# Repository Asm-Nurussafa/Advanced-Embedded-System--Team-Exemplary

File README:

To see the results of the final simulation ,simulate the fin_decode_TB in modelsim,found in the project folder.

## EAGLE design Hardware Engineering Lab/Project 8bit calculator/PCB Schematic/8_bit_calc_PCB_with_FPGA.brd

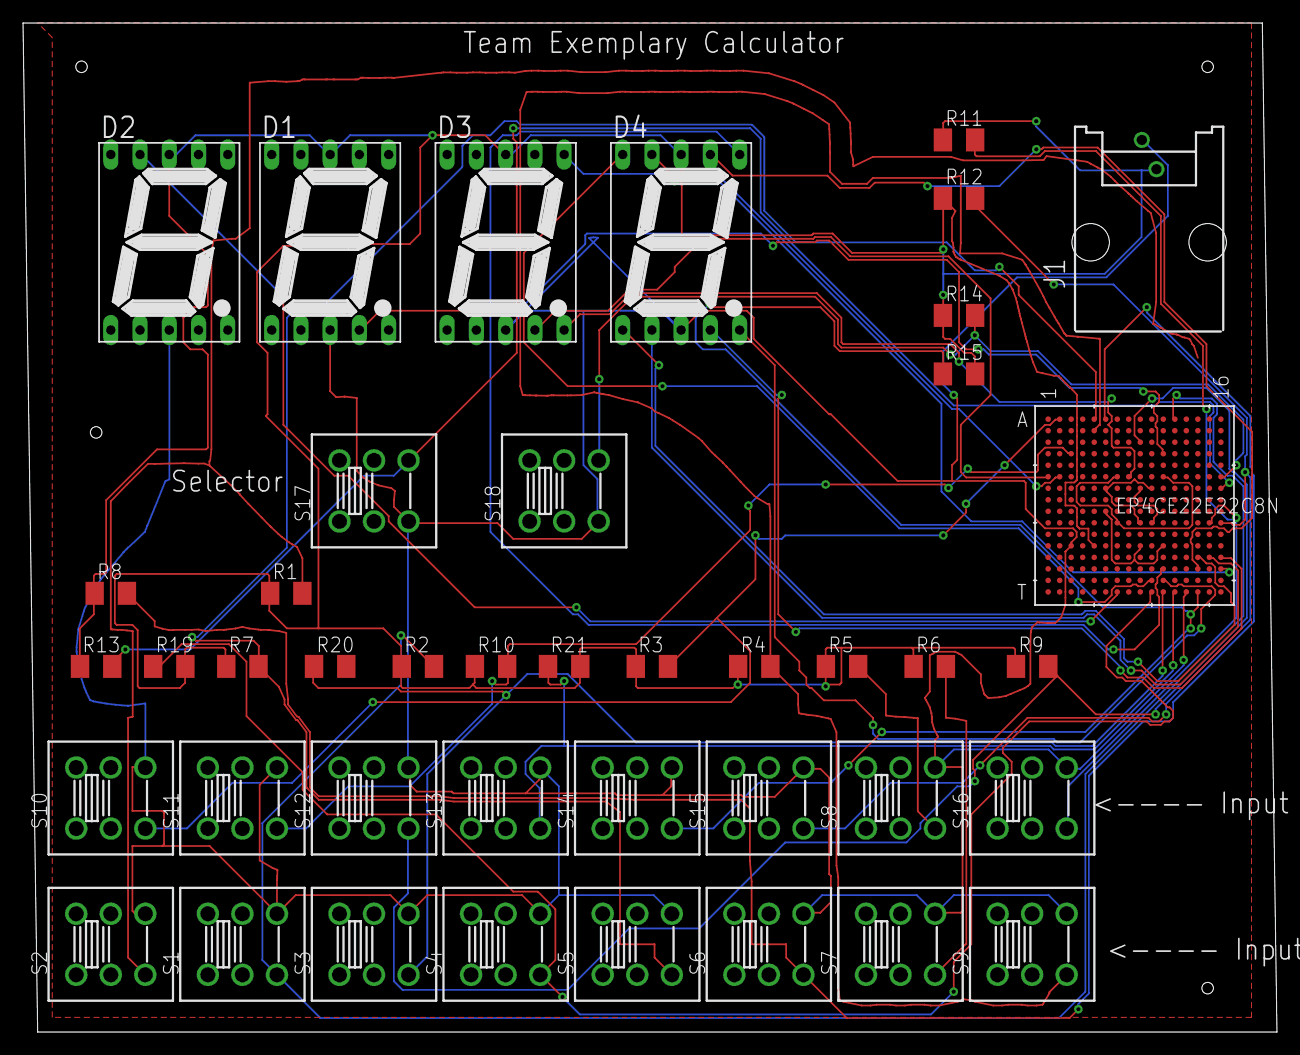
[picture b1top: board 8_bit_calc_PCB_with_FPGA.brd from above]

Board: 2 copper layers, 108.9 x 87.6 mm, 42 parts (0 on the bottom side), 59 nets.

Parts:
D1, D2, D3, D4: 7SEG-13
J1: 215876-7
R1, R2, R3, R4, R5, R6, R7, R8, R9, R10, R11, R12, R13, R14, R15, R19, R20, R21: M1206
S1, S2, S3, S4, S5, S6, S7, S8, S9, S10, S11, S12, S13, S14, S15, S16, S17, S18: 2P2T
U1: EP4CE22E22C8N; FBGA256_THIN_WIRE-BOND-A:1.55_

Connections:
GND: D1.8, D2.8, D3.8, D4.8, J1.2, R1.1, R2.1, R3.1, R9.1, R10.1, R11.1, R12.1, R13.1, R14.1, R15.2, R19.2, R21.2, U1.M5
unnamed: D2.4, U1.T3
unnamed: D2.2, U1.T2
unnamed: D2.6, U1.T4
unnamed: D2.7, U1.T5
unnamed: D2.9, U1.T7
unnamed: D2.10, U1.R6
unnamed: D2.1, U1.R7
unnamed: D3.1, U1.E8
unnamed: D1.5, U1.D16
unnamed: R2.2, S1.3.2
unnamed: R1.2, S2.3.2
unnamed: D1.10, U1.D15
unnamed: D1.9, U1.D14
unnamed: D1.7, U1.D13
unnamed: D1.1, U1.C16
unnamed: D1.6, U1.D12
unnamed: D1.4, U1.D11
unnamed: D1.2, U1.D10
unnamed: D3.2, U1.E9
unnamed: D3.4, U1.F1
unnamed: D3.6, U1.F2
unnamed: D3.7, U1.F3
unnamed: D3.5, U1.F8
unnamed: D3.10, U1.F9
unnamed: D2.5, U1.A11
unnamed: R10.2, S11.3.2, U1.D3
unnamed: R9.2, S12.3.2
unnamed: R3.2, S10.3.2, U1.A2
unnamed: R4.2, S9.3.2, U1.B5
unnamed: R5.2, S8.3.2, U1.B4
unnamed: R11.2, S16.3.2, U1.K15
unnamed: R12.2, S15.3.2, U1.K16
unnamed: R6.2, S7.3.2, U1.B3
unnamed: R7.2, S5.3.2, U1.A5
unnamed: D4.5, U1.R11
unnamed: R14.2, S18.3.1, U1.F16
unnamed: R13.2, S17.3.1, U1.G16
unnamed: D4.1, U1.N14
unnamed: D4.2, U1.N15
unnamed: D4.4, U1.N16
unnamed: D4.6, U1.P11
unnamed: D4.7, U1.P14
unnamed: D4.9, U1.P16
unnamed: D4.10, U1.R10
unnamed: R15.1, S14.3.2, U1.T14
unnamed: R19.1, S4.3.2, U1.T10
unnamed: R20.1, S3.3.2, U1.T11
unnamed: R21.1, S13.3.2, U1.T12
unnamed: R4.1, R5.1, R6.1, R7.1, R8.1
unnamed: R8.2, S6.3.2, U1.A6
VCC: D1.3, D2.3, D3.3, D4.3, J1.1, S1.3.1, S2.3.1, S3.3.1, S4.3.1, S5.3.1, S6.3.1, S7.3.1, S8.3.1, S9.3.1, S10.3.1, S11.3.1, S12.3.1, S13.3.1, S14.3.1, S15.3.1, S16.3.1, S17.3.2, S18.3.2, U1.M3
VCCINT: U1.J6, U1.M9, U1.M11
VCCINT_2: U1.F7, U1.F11, U1.K7
VCCINT_3: U1.G6, U1.G10, U1.K9
VCCINT_4: U1.G7, U1.H11, U1.L6
VCCINT_5: U1.G8, U1.J12
VCCINT_6: U1.G9, U1.K10
VCCINT_7: U1.H6, U1.K11

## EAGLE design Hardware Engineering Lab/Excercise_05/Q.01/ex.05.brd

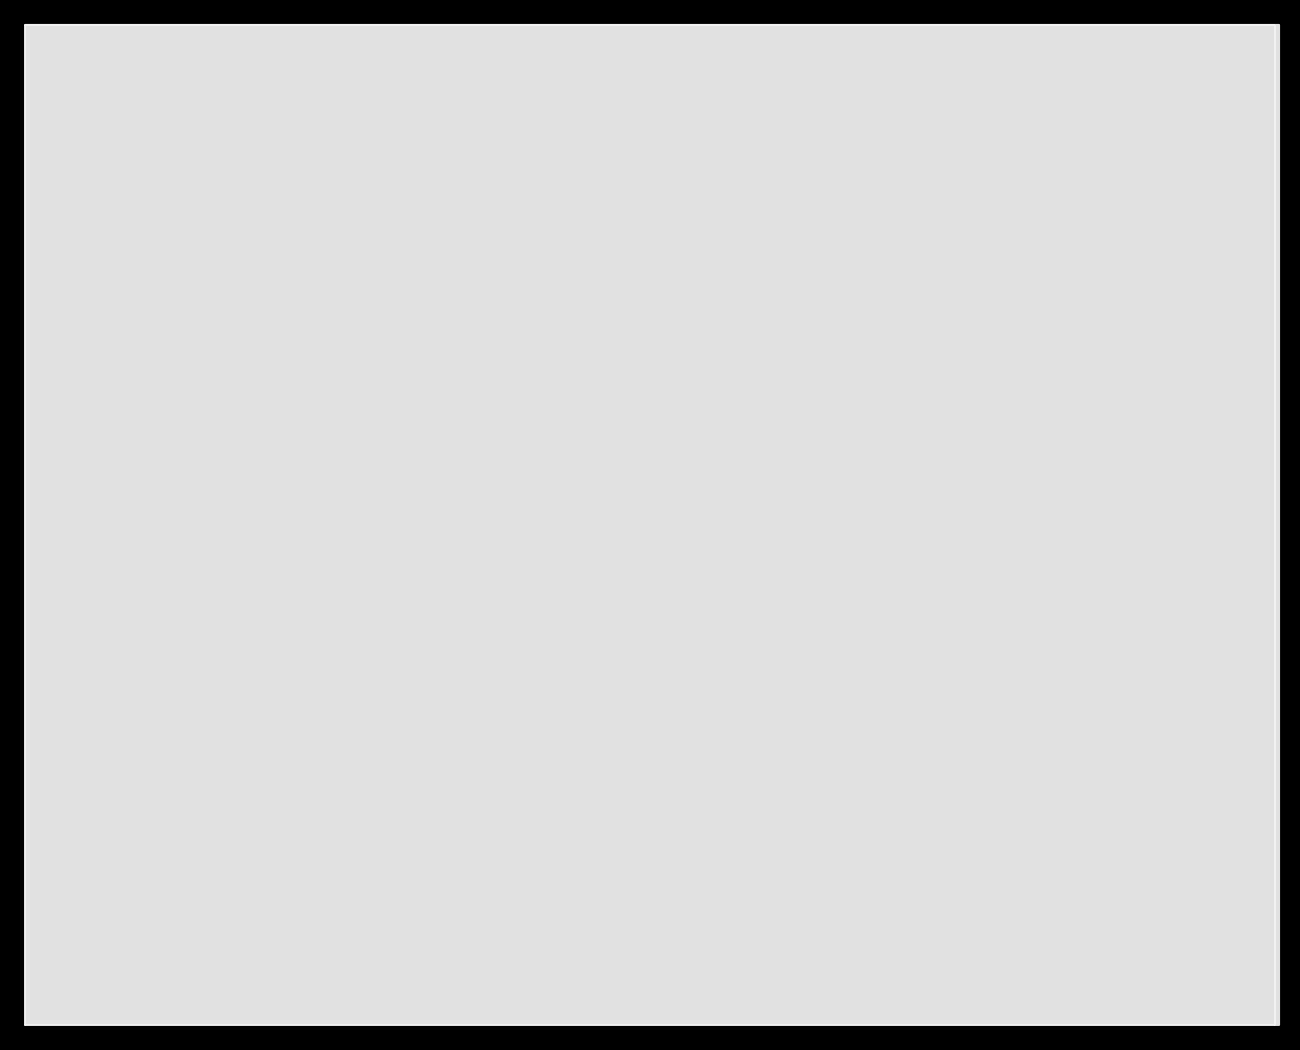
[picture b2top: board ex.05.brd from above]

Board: 2 copper layers, 100.0 x 80.0 mm, 14 parts (0 on the bottom side), 22 nets.

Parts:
C1, C2: 10nF; CAP-PTH-10MM
D1, D2, D3: PINK; LED-1206
J1: POWER_JACK; POWER_JACK_PTH
J2: 794681-8
J3: AVR_SPI_PROG_3X2SMD; 2X3_SMT_POSTS
J5: 1X06_LOCK
R1, R2, R3, R4: PMD
U1: 328P; DIP28

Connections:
DTR: C2.1, J5.1
GND: C1.2, J1.GND, J1.GNDBREAK, J2.6, J3.6, J5.6, R1.2, R2.2, R3.2, U1.8, U1.22
MISO: J3.1, U1.18
MOSI: J3.4, U1.17
unnamed: D3.A, U1.14
unnamed: D2.A, U1.15
unnamed: D1.A, U1.16
unnamed: D1.C, R1.1
unnamed: D2.C, R2.1
unnamed: D3.C, R3.1
unnamed: J2.7, U1.23
unnamed: J2.5, U1.24
unnamed: J2.3, U1.25
unnamed: J2.1, U1.26
unnamed: J2.4, U1.28
unnamed: J2.2, U1.27
RESET: C2.2, J3.5, R4.2, U1.1
RX: J5.3, U1.2
SCK: J3.3, U1.19
TX: J5.2, U1.3
VCC: C1.1, J1.PWR, J2.8, J5.4
VCCIO: J3.2, R4.1, U1.7, U1.20

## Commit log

2022-05-05 creation of Folders for Each subject
2022-05-05 VHDL code for Half Adder and the testbench
2022-05-06 full adder VHDL code
2022-05-07 Create BCD to 7seg decorder
    ABCD as BDC and PQRS TUV as segments
2022-05-07 update
    upadte
2022-05-12 rename
    rename
2022-05-12 rearranging
2022-05-12 update
    Rearrange properply and added all task sol_n
2022-05-13 initial solution for ex_03 _b
2022-05-13 info
2022-05-17 creation of new folder for documentation
2022-05-17 Intermediate document upload
    the first version of the documentation
2022-05-17 creation of folder for documentation
2022-05-17 intermediate documentation
    first version of document
2022-05-17 unwanted file deletion
2022-05-17 deleting empty file
2022-05-22 Project
2022-05-23 8 bit multiplier working
    part of the final project
2022-05-24 Arduino code one sesnor and mqtt
    initial upload of the project
2022-05-24 project code
    sensor data and mqtt
2022-05-26 with std_logic
    all files updated with std_logic
    multiplier has some issues with l.s.b
2022-05-26 all files updated with std_logic
    multiplier has some issues with l.s.b
2022-05-27 Create deleteme
2022-05-27 Multiplexer
    Test_bench does not simulate for some reason
2022-05-27 Sequential 4 to 1 multiplexer
    TB does not work for some reason
2022-05-27 8 bit reg
    update
2022-06-03 Create delete me
2022-06-03 initial code with one sensor
    other sesnors and actuators need to be merged in the code and MQTT part for them as well
2022-06-03 Create python_code.py
    code to automate the process
2022-06-05 16_bit decorder working
    led outputs in 7 bit
2022-06-05 Create 16_b_mux.vhd
    mux
2022-06-06 testcode
    this code is to check if its working can be deleted later on
2022-06-06 ignore
2022-06-07 update clean
    update
2022-06-07 test update
2022-06-07 connecting decorder with fix _calculator
    looks like the code is wroking well, need to test and also as next step write test bench for all the induvidual components
2022-06-07 update to multiplier
2022-06-09 TB_ for fin_decode available now
    TB_for final result is available now
2022-06-09 report statement included
    test bench with report statement updated
2022-06-10 Create README
    instruction for final simulation
2022-06-10 creating folder for the pcb design
2022-06-15 arranging properly
2022-06-17 eps32 and arduino MQTT codes
2022-06-17 not required anymore,updated code available
2022-06-17 not required anymore
2022-06-18 arduino code update
2022-06-22 Documentation, python code, diagrams updated
2022-06-23 pcb files upload
    uploading V01 of PCB design
2022-06-23 deleting delete me file
2022-06-23 information about the overall single code file
2022-06-23 creating a folder for the presentation
2022-06-23 intial step for presenation slides
2022-06-23 initially maping ports using the .ucf format
    bitstream file is not being able to generate
2022-06-23 uploading pcb files
2022-06-23 Pcb layout 2
2022-06-23 layout update
2022-06-24 initial draft
2022-06-24 wrong file
2022-06-24 updated version available
2022-06-24 Protocol update
2022-06-24 Divider 16 vhd and testbench
2022-06-24 comments added to the vhdl code
2022-06-24 not necessary
2022-06-24 Draft Documentation
2022-06-24 comments added to vhdl code
2022-06-24 document update
2022-06-24 update paper
2022-06-24 paper update
2022-06-24 new version available
2022-06-24 Updated protocol
2022-06-24 updated pdf documentation
2022-06-24 Updated protocol file
2022-06-24 Fixed folders
2022-06-24 newest version
2022-06-24 Updated documentation
2022-06-28 Final Presentation Slides
2022-06-28 Final Presentation slides updated
2022-06-28 later version
2022-06-30 Link to video demo
2022-07-06 wrong copy
2022-07-06 extra copy
2022-07-06 Final presentation files
2022-07-06 pcb Update

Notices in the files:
parts and their libraries:
SparkFun-Capacitors: Licensing: Creative Commons ShareAlike 4.0 International - https://creativecommons.org/licenses/by-sa/4.0
COPYRIGHT: Copyright (C) 2022 Ultra Librarian. All rights reserved.
